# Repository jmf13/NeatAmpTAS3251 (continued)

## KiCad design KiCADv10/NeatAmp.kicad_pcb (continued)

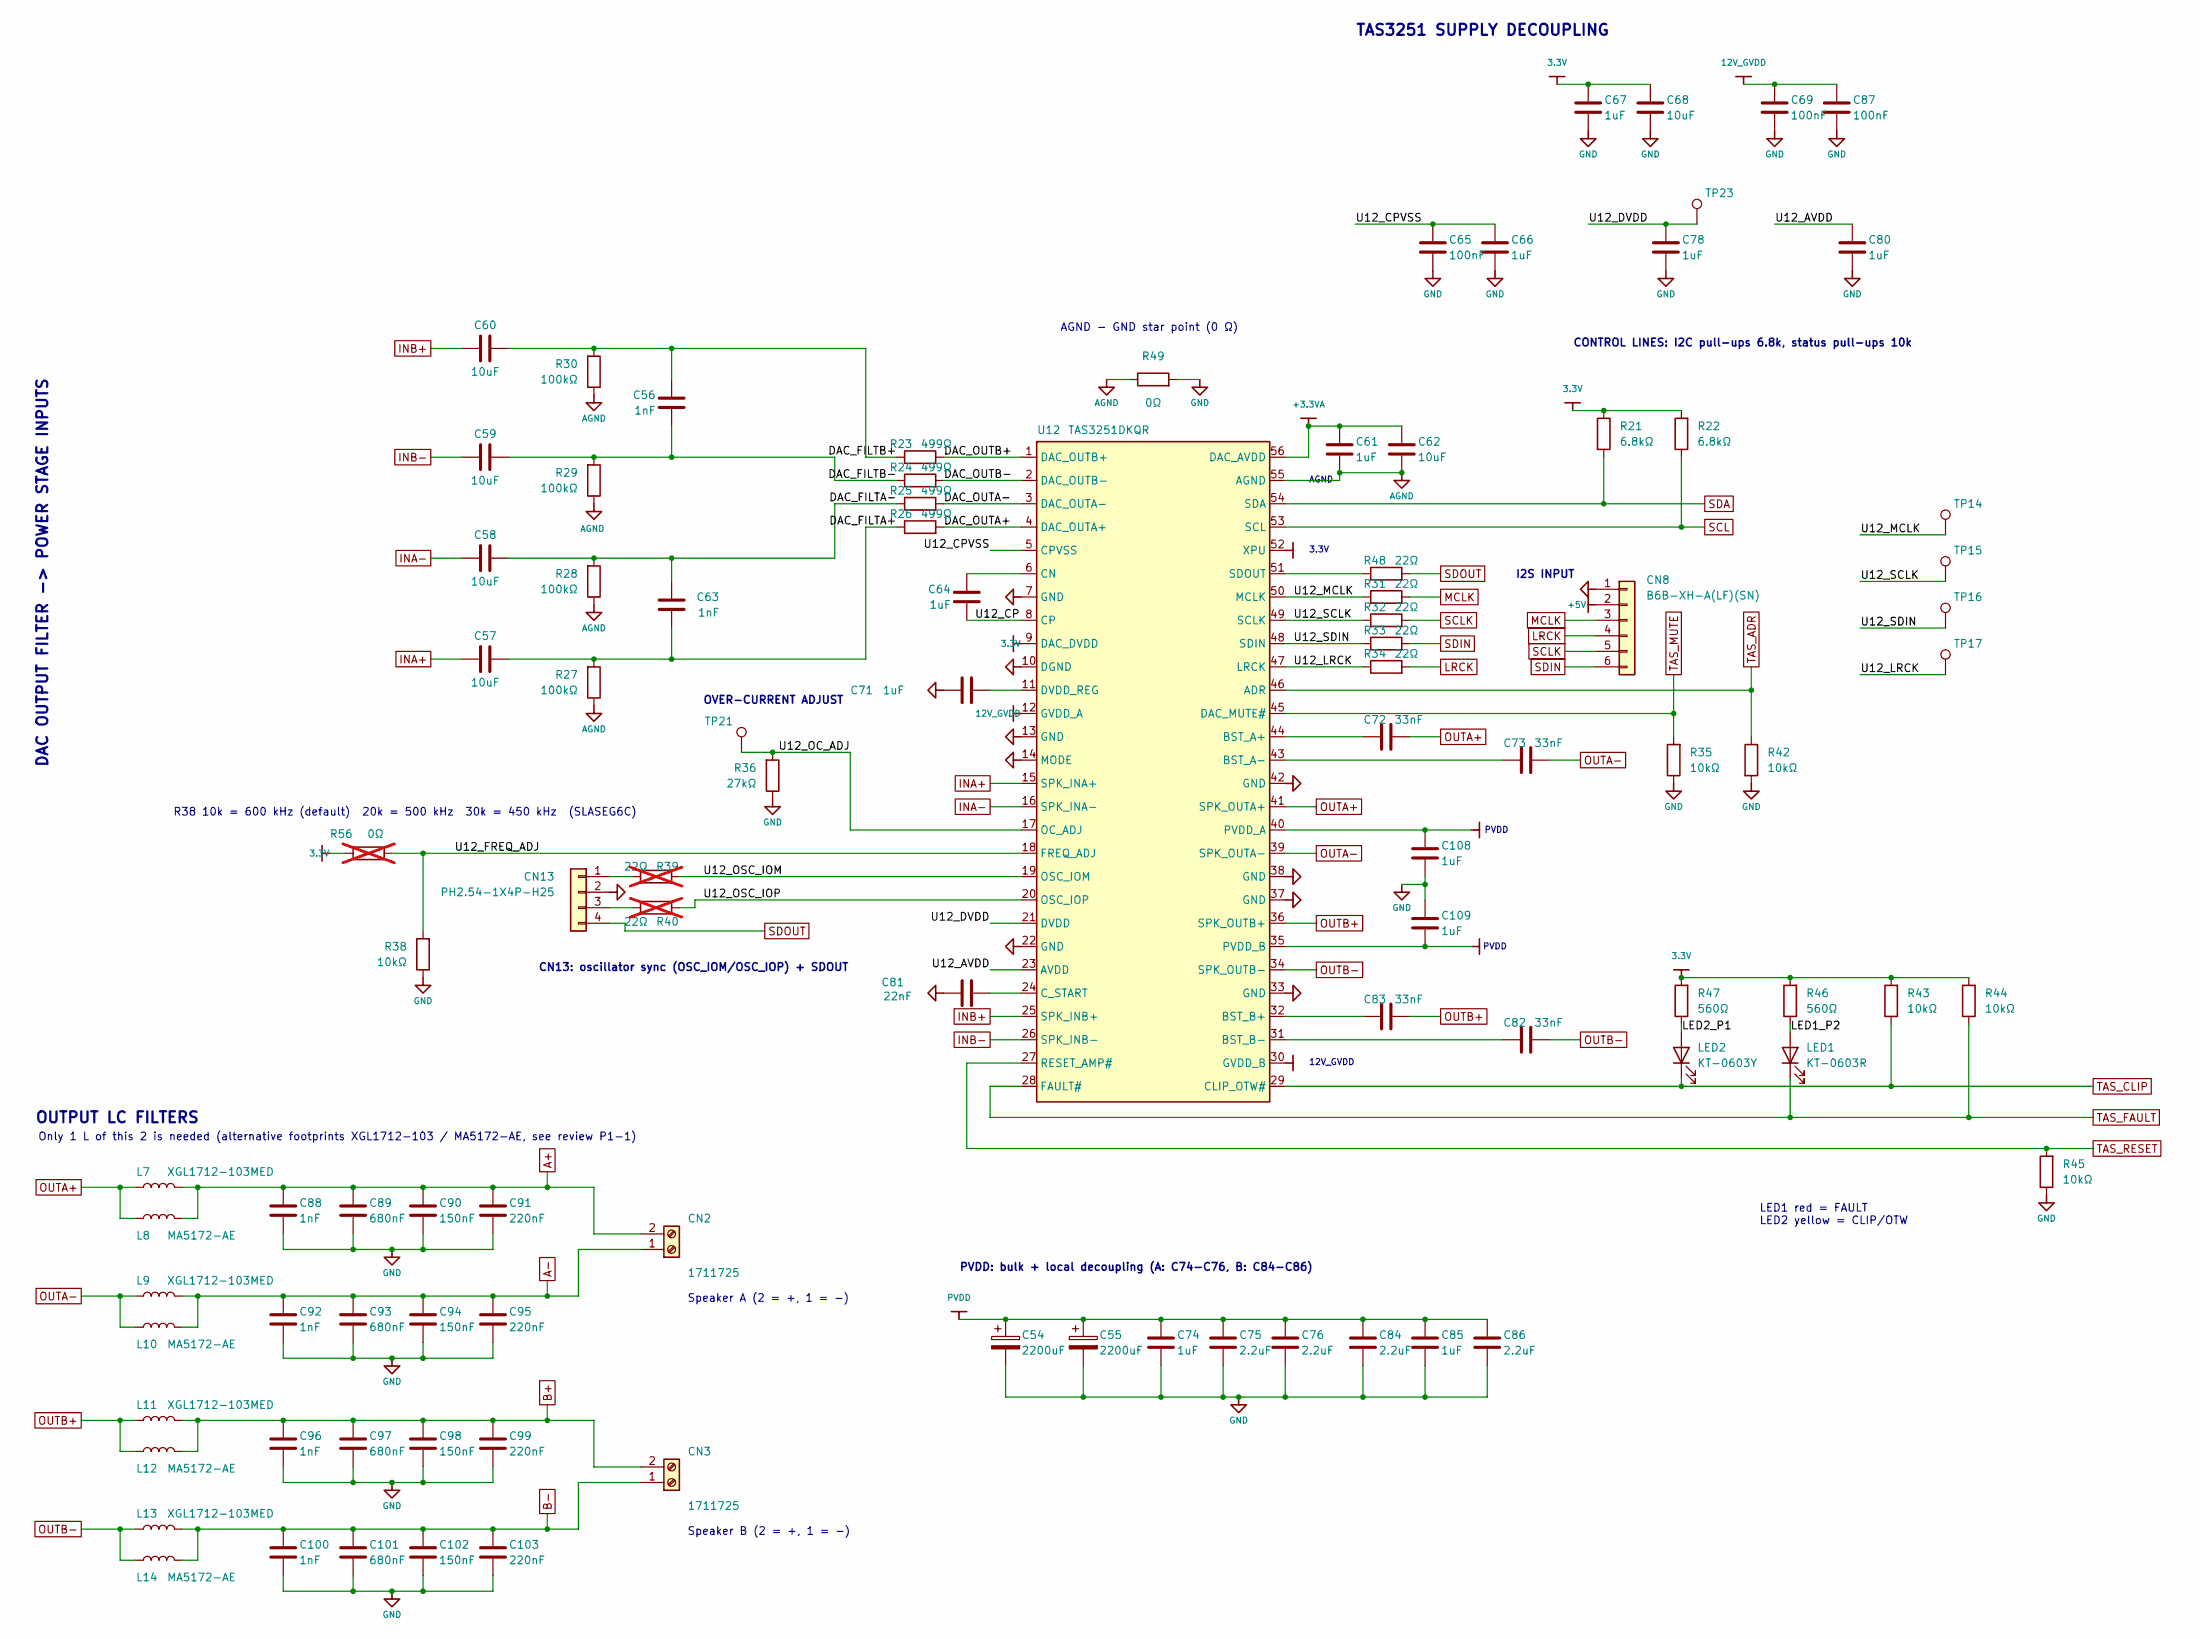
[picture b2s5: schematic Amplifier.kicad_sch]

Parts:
C54, C55: 2200uF; CAP-TH_BD18.0-P7.5-D0.8-FD; MPN NXA 63V 2200UF 18*40; LCSC C2827938
C56, C63, C88, C92, C96, C100: 1nF; C0402; MPN 0402CG102J500NT; LCSC C53547
C57, C58, C59, C60, C62, C68: 10uF; C1210; MPN CL32B106KBJNNNE; LCSC C138687
C61, C64, C66, C67, C71, C78: 1uF; C0603; MPN CL10B105KB8NQNC; LCSC C5199872
C65, C69, C87: 100nF; C0402; MPN CL05B104KB54PNC; LCSC C307331
C72, C73, C82, C83: 33nF; C0805; MPN 0805B333K500NT; LCSC C1739
C74, C80, C85, C108, C109: 1uF; C1206; MPN CL31B105KCHNNNE; LCSC C13832
C75, C76, C84, C86: 2.2uF; C1206; MPN CL31B225KCHSNNE; LCSC C170101
C81: 22nF; C1206; MPN CC1206JRX7R9BB223; LCSC C527321
C89, C93, C97, C101: 680nF; CAP-TH_L26.0-W12.0-P22.50-D0.8; MPN MKP684K310A01; LCSC C434162
C90, C94, C98, C102: 150nF; CAP-TH_L18.0-W10.0-P15.00-D1.2; MPN MKP154K310A01; LCSC C434218
C91, C95, C99, C103: 220nF; CAP-TH_L18.3-W10.0-P15.00-D1.0; MPN MKP224K310A08 THB; LCSC C434236
CN2, CN3: 1711725; CONN-TH_MKDS3-2-5.08; MPN 1711725; LCSC C89120
CN8: B6B-XH-A(LF)(SN); CONN-TH_6P-P2.50_B6B-XH-A-LF-SN; MPN B6B-XH-A(LF)(SN); LCSC C144397
CN13: PH2.54-1X4P-H25; HDR-TH_4P-P2.54-V-M; MPN PH2.54-1X4P-H25; LCSC C42431808
L7, L9, L11, L13: XGL1712-103MED; IND-SMD_L17.2-W18.2
L8, L10, L12, L14: MA5172-AE; MA5172AE
LED1: KT-0603R; LED-SMD_L1.6-W0.8-R-RD; MPN KT-0603R; LCSC C2286
LED2: KT-0603Y; LED-SMD_L1.6-W0.8-R-RD; MPN KT-0603Y; LCSC C2287
R21, R22: 6.8kΩ; R0402; MPN 0402WGF6801TCE; LCSC C25917
R23, R24, R25, R26: 499Ω; R0603; MPN TD03G4990BT; LCSC C666886
R27, R28, R29, R30: 100kΩ; R0603; MPN TD03G1003BT; LCSC C667147
R31, R32, R33, R34, R48: 22Ω; R0402; MPN 0402WGF220JTCE; LCSC C25092
R35, R38, R42, R43, R44, R45: 10kΩ; R0603; MPN 0603WAF1002T5E; LCSC C25804
R36: 27kΩ; R0402; MPN 0402WGF2702TCE; LCSC C25771
R39, R40: 22Ω; R0603; MPN 0603WAF220JT5E; LCSC C23345; not fitted
R46, R47: 560Ω; R0402; MPN 0402WGF5600TCE; LCSC C25126
R49: 0Ω; R1206; MPN 1206W4F0000T5E; LCSC C17888
R56: 0Ω; R0603; MPN 0603WAJ0000T5E; LCSC C21189; not fitted
TP14, TP15, TP16, TP17, TP21, TP23: Test-Point; TestPoint_Pad_D1.0mm
U12: TAS3251DKQR; TAS3251_DKQ_HSSOP-56_Heatsink_ATS-TI1OP-1099; MPN TAS3251DKQR; LCSC C544648

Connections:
3.3V: C67.2, C68.1, R21.1, R22.2, R43.2, R44.2, R46.2, R47.2, R56.1, U12.9 (DAC_DVDD), U12.52 (XPU); also elsewhere on the board
12V_GVDD: C69.2, C87.2, U12.12 (GVDD_A), U12.30 (GVDD_B); also elsewhere on the board
+3.3VA: C61.2, C62.1, U12.56 (DAC_AVDD); also elsewhere on the board
+5V: CN8.2; also elsewhere on the board
/Amplifier/DAC_FILTA+: C57.1, C63.2, R26.1, R27.2
/Amplifier/DAC_FILTA-: C58.1, C63.1, R25.1, R28.2
/Amplifier/DAC_FILTB+: C56.2, C60.1, R23.1, R30.2
/Amplifier/DAC_FILTB-: C56.1, C59.1, R24.1, R29.2
/Amplifier/DAC_OUTA+: R26.2, U12.4 (DAC_OUTA+)
/Amplifier/DAC_OUTA-: R25.2, U12.3 (DAC_OUTA-)
/Amplifier/DAC_OUTB+: R23.2, U12.1 (DAC_OUTB+)
/Amplifier/DAC_OUTB-: R24.2, U12.2 (DAC_OUTB-)
/Amplifier/LED1_P2: LED1.2 (A), R46.1
/Amplifier/LED2_P1: LED2.2 (A), R47.1
/Amplifier/U12_AVDD: C80.2, U12.23 (AVDD)
/Amplifier/U12_CP: C64.2, U12.8 (CP)
/Amplifier/U12_CPVSS: C65.2, C66.2, U12.5 (CPVSS)
/Amplifier/U12_DVDD: C78.2, TP23.1 (1_1), U12.21 (DVDD)
/Amplifier/U12_FREQ_ADJ: R38.2, R56.2, U12.18 (FREQ_ADJ)
/Amplifier/U12_LRCK: R34.1, TP17.1 (1_1), U12.47 (LRCK)
/Amplifier/U12_MCLK: R31.1, TP14.1 (1_1), U12.50 (MCLK)
/Amplifier/U12_OC_ADJ: R36.2, TP21.1 (1_1), U12.17 (OC_ADJ)
/Amplifier/U12_OSC_IOM: R39.2, U12.19 (OSC_IOM)
/Amplifier/U12_OSC_IOP: R40.2, U12.20 (OSC_IOP)
/Amplifier/U12_SCLK: R32.1, TP15.1 (1_1), U12.49 (SCLK)
/Amplifier/U12_SDIN: R33.1, TP16.1 (1_1), U12.48 (SDIN)
A+: C88.2, C89.2, C90.2, C91.2, CN2.2, L7.2, L8.2
A-: C92.2, C93.2, C94.2, C95.2, CN2.1, L9.2, L10.2
AGND: C61.1, C62.2, R27.1, R28.1, R29.1, R30.1, R49.1, U12.55 (AGND); also elsewhere on the board
B+: C96.2, C97.2, C98.2, C99.2, CN3.2, L11.2, L12.2
B-: C100.2, C101.2, C102.2, C103.2, CN3.1, L13.2, L14.2
GND: C54.2, C55.2, C65.1, C66.1, C67.1, C68.2, C69.1, C71.1, C74.2, C75.2, C76.2, C78.1, C80.1, C81.1, C84.1, C85.1, C86.1, C87.1, C88.1, C89.1, C90.1, C91.1, C92.1, C93.1, C94.1, C95.1, C96.1, C97.1, C98.1, C99.1, C100.1, C101.1, C102.1, C103.1, C108.1, C109.2, CN8.1, CN13.2, R35.1, R36.1, R38.1, R42.2, R45.1, R49.2, U12.7 (GND), U12.10 (DGND), U12.13 (GND), U12.14 (MODE), U12.22 (GND), U12.33 (GND), U12.37 (GND), U12.38 (GND), U12.42 (GND); also elsewhere on the board
INA+: C57.2, U12.15 (SPK_INA+)
INA-: C58.2, U12.16 (SPK_INA-)
INB+: C60.2, U12.25 (SPK_INB+)
INB-: C59.2, U12.26 (SPK_INB-)
LRCK: CN8.4, R34.2
MCLK: CN8.3, R31.2
unnamed: CN13.1, R39.1
unnamed: CN13.3, R40.1
unnamed: C72.2, U12.44 (BST_A+)
unnamed: C73.2, U12.43 (BST_A-)
unnamed: C83.2, U12.32 (BST_B+)
unnamed: C82.2, U12.31 (BST_B-)
unnamed: C64.1, U12.6 (CN)
unnamed: C81.2, U12.24 (C_START)
unnamed: C71.2, U12.11 (DVDD_REG)
unnamed: R48.1, U12.51 (SDOUT)
OUTA+: C72.1, L7.1, L8.1, U12.41 (SPK_OUTA+)
OUTA-: C73.1, L9.1, L10.1, U12.39 (SPK_OUTA-)
OUTB+: C83.1, L11.1, L12.1, U12.36 (SPK_OUTB+)
OUTB-: C82.1, L13.1, L14.1, U12.34 (SPK_OUTB-)
PVDD: C54.1, C55.1, C74.1, C75.1, C76.1, C84.2, C85.2, C86.2, C108.2, C109.1, U12.35 (PVDD_B), U12.40 (PVDD_A); also elsewhere on the board
SCL: R22.1, U12.53 (SCL); also elsewhere on the board
SCLK: CN8.5, R32.2
SDA: R21.2, U12.54 (SDA); also elsewhere on the board
SDIN: CN8.6, R33.2
SDOUT: CN13.4, R48.2
TAS_ADR: R42.1, U12.46 (ADR); also elsewhere on the board
TAS_CLIP: LED2.1 (K), R43.1, U12.29 (CLIP_OTW#); also elsewhere on the board
TAS_FAULT: LED1.1 (K), R44.1, U12.28 (FAULT#); also elsewhere on the board
TAS_MUTE: R35.2, U12.45 (DAC_MUTE#); also elsewhere on the board
TAS_RESET: R45.2, U12.27 (RESET_AMP#); also elsewhere on the board

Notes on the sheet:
AGND
I2S INPUT
PVDD
OVER-CURRENT ADJUST
OUTPUT LC FILTERS
CONTROL LINES: I2C pull-ups 6.8k, status pull-ups 10k
CN13: oscillator sync (OSC_IOM/OSC_IOP) + SDOUT
PVDD: bulk + local decoupling (A: C74-C76, B: C84-C86)
Only 1 L of this 2 is needed (alternative footprints XGL1712-103 / MA5172-AE, see review P1-1)
AGND - GND star point (0 Ω)
LED1 red = FAULT LED2 yellow = CLIP/OTW
3.3V
12V_GVDD
R38 10k = 600 kHz (default) 20k = 500 kHz 30k = 450 kHz (SLASEG6C)
DAC OUTPUT FILTER -> POWER STAGE INPUTS
Speaker A (2 = +, 1 = -)
TAS3251 SUPPLY DECOUPLING
Speaker B (2 = +, 1 = -)

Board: 4 copper layers, 234 parts (7 on the bottom side), 137 nets, no tracks yet.

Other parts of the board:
MH1, MH2, MH3, MH4, MH5, MH6, MH7: M3; MountingHole_3.2mm_M3_Pad_7mm

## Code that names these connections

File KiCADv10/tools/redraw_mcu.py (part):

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P('USBC1', 'USBC', 28, 50, 0, txt=(-6, -16, -6, -14, 'left'))
# right pins x=38: VBUS 39/41, CC1 44, CC2 46, DP1 50, DP2 52, DN1 54, DN2 56, SBU1 59, SBU2 61
# bottom y=69: GND x=27/30, SHIELD x=24
W((38, 39), (40, 39)); W((38, 41), (40, 41), (40, 39), (40, 30), (57, 30))   # VBUS -> VBUS1 rail y=30
PW('VBUS1', 44, 30)
P('C107', 'C', 50, 33, 180)                              # pin2 (50,30)=VBUS1
PW('GND', 50, 36)
P('L6', 'FB', 60, 30, 270, txt=(0, -5, 0, -3, None))                      # pin2 (57,30)=VBUS1 pin1 (63,30)
W((63, 30), (77, 30))
LBL('C46_P2', 64, 30)
P('C46', 'C', 72, 33, 180)
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          22: 'U6_IO14', 23: 'U6_IO21'}
for n, name in bottom.items():
    lbl_down(name, 149 + 2 * (n - 15), 139)
lbl_down('ESP_TAS_ADR', 159, 139, stub=13, glob=True)    # 20, long stub clears the neighbouring labels
for k, (n, name) in enumerate([(26, 'SCL'), (25, 'DSP_SELFBOOT'), (24, 'DSP_RESET')]):
    x, y = 149 + 2 * (n - 15), 142 + 2 * k                # fan out to the right
    W((x, 139), (x, y), (186, y))
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PW('GND', 46, 98); PW('GND', 56, 98)
T('U6 3V3 decoupling (at module pin 2)', 62, 95)
P('SW1', 'SW4', 44, 110, 0, txt=(-4, -6.5, 0, -6.5, 'left'))  # 1 (40,106) 2 (48,106) 3 (40,114) 4 (48,114)
P('C47', 'C', 36, 110, 180, txt='l')                     # pin2 (36,107)=SW1_P1 pin1 (36,113)
W((40, 106), (36, 106), (36, 107)); W((36, 113), (36, 114), (40, 114))
LBL('SW1_P1', 36, 106, ang=180)
PW('GND', 48, 114)
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
# ====================================================== I2C to DSP (22 ohm series)
GL('SDA', 196, 154, ang=180)
P('R19', 'R', 202, 154, 270, txt=(-3, -2, 1, -2, 'left'))   # pin2 (199,154)=SDA pin1 (205,154)=DSP_SDA
W((196, 154), (199, 154)); W((205, 154), (208, 154)); GL('DSP_SDA', 208, 154, ang=0)
GL('SCL', 196, 160, ang=180)
P('R20', 'R', 202, 160, 270, txt=(-3, -2, 1, -2, 'left'))
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PW('3.3V', 204, 166)
P('TP12', 'TP', 207, 172, 0, txt='tp')
P('SW2', 'SW4', 214, 176, 0, txt=(5, 5.5, 5, 7.5, 'left'))  # 1 (210,172) 2 (218,172) 3 (210,180) 4 (218,180)
P('C51', 'C', 222, 176, 180)                             # pin2 (222,173)=SW2_P2 pin1 (222,179)
W((218, 172), (222, 172), (222, 173)); W((222, 179), (222, 180), (218, 180))
LBL('SW2_P2', 222, 172)
PW('GND', 210, 180)
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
